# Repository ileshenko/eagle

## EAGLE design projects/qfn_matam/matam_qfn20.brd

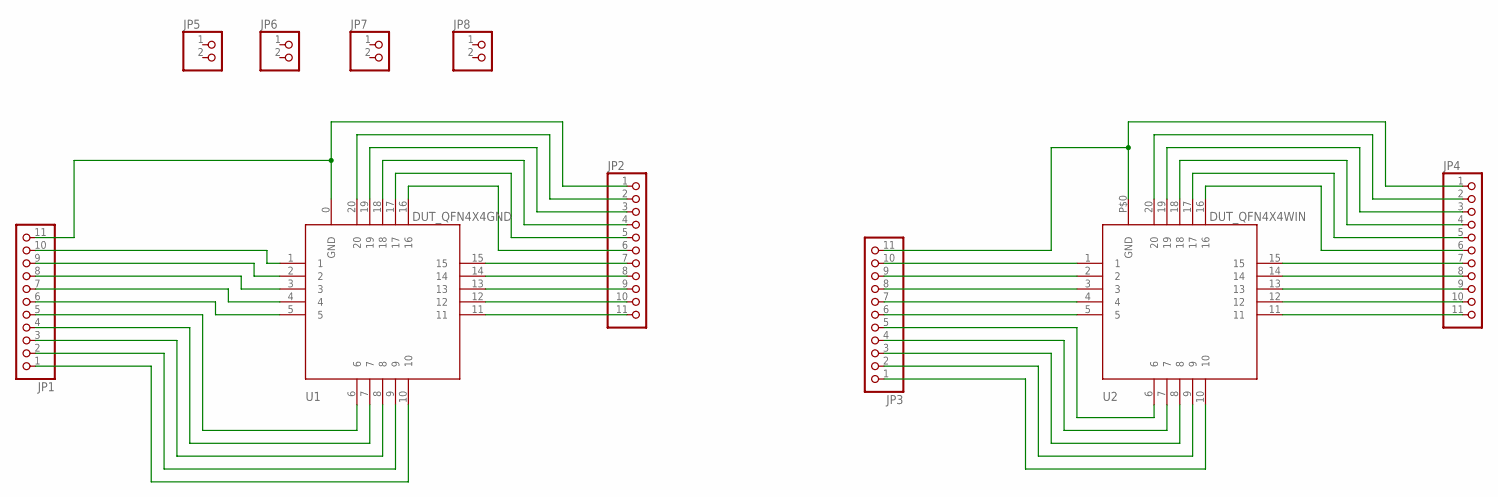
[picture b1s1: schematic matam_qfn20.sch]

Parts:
JP1, JP2, JP3, JP4: PINHD-1X11; 1X11
JP5, JP6, JP7, JP8: PINHD-1X2/90; 1X02/90
U1: DUT_QFN4X4GND; QFN20_4X4_GND
U2: DUT_QFN4X4WIN; QFN20_4X4_WINDOW

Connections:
unnamed: JP1.11, JP2.1, U1.0 (GND)
unnamed: JP1.10, U1.1
unnamed: JP1.9, U1.2
unnamed: JP1.8, U1.3
unnamed: JP1.7, U1.4
unnamed: JP1.6, U1.5
unnamed: JP1.5, U1.6
unnamed: JP1.4, U1.7
unnamed: JP1.3, U1.8
unnamed: JP1.2, U1.9
unnamed: JP1.1, U1.10
unnamed: JP2.11, U1.11
unnamed: JP2.10, U1.12
unnamed: JP2.9, U1.13
unnamed: JP2.8, U1.14
unnamed: JP2.7, U1.15
unnamed: JP2.6, U1.16
unnamed: JP2.5, U1.17
unnamed: JP2.4, U1.18
unnamed: JP2.3, U1.19
unnamed: JP2.2, U1.20
unnamed: JP3.10, U2.1
unnamed: JP3.9, U2.2
unnamed: JP3.8, U2.3
unnamed: JP3.7, U2.4
unnamed: JP3.6, U2.5
unnamed: JP3.5, U2.6
unnamed: JP3.4, U2.7
unnamed: JP3.3, U2.8
unnamed: JP3.2, U2.9
unnamed: JP3.1, U2.10
unnamed: JP3.11, JP4.1, U2.P$0 (GND)
unnamed: JP4.11, U2.11
unnamed: JP4.10, U2.12
unnamed: JP4.9, U2.13
unnamed: JP4.8, U2.14
unnamed: JP4.7, U2.15
unnamed: JP4.6, U2.16
unnamed: JP4.5, U2.17
unnamed: JP4.4, U2.18
unnamed: JP4.3, U2.19
unnamed: JP4.2, U2.20

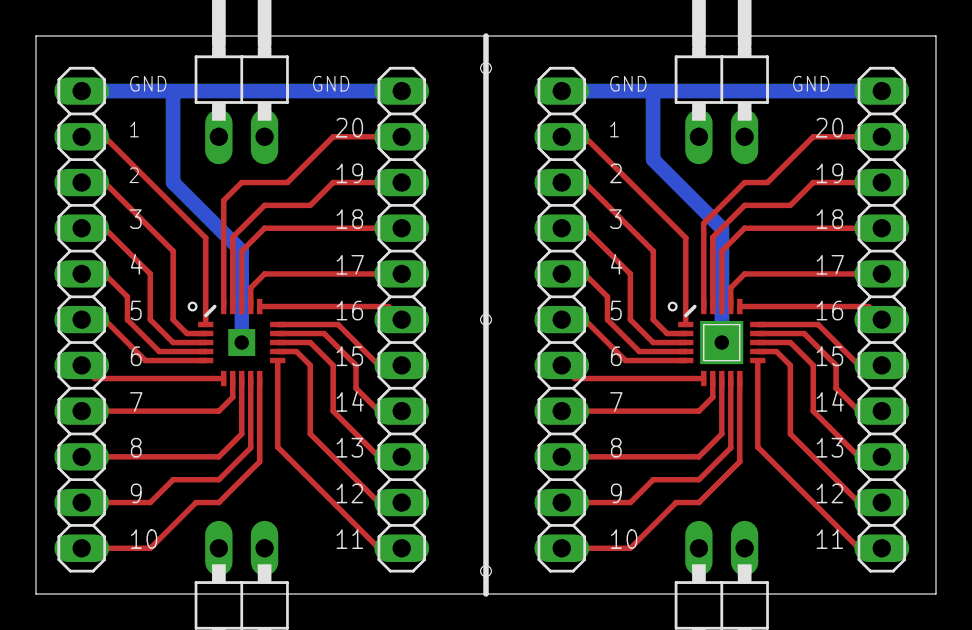
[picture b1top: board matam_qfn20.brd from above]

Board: 2 copper layers, 50.0 x 31.0 mm, 10 parts (0 on the bottom side), 42 nets.

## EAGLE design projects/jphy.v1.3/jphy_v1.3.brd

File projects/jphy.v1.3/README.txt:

Ver.1.3
Use IPC-73511 libraries for R and C

ver.1.2

Changes:
- Use 0805 devices instead of 1206;
- Use SMD LED and resistor;
- Change RJ45 drills from 2.54mm to 3mm.
- Change RJ45 ...

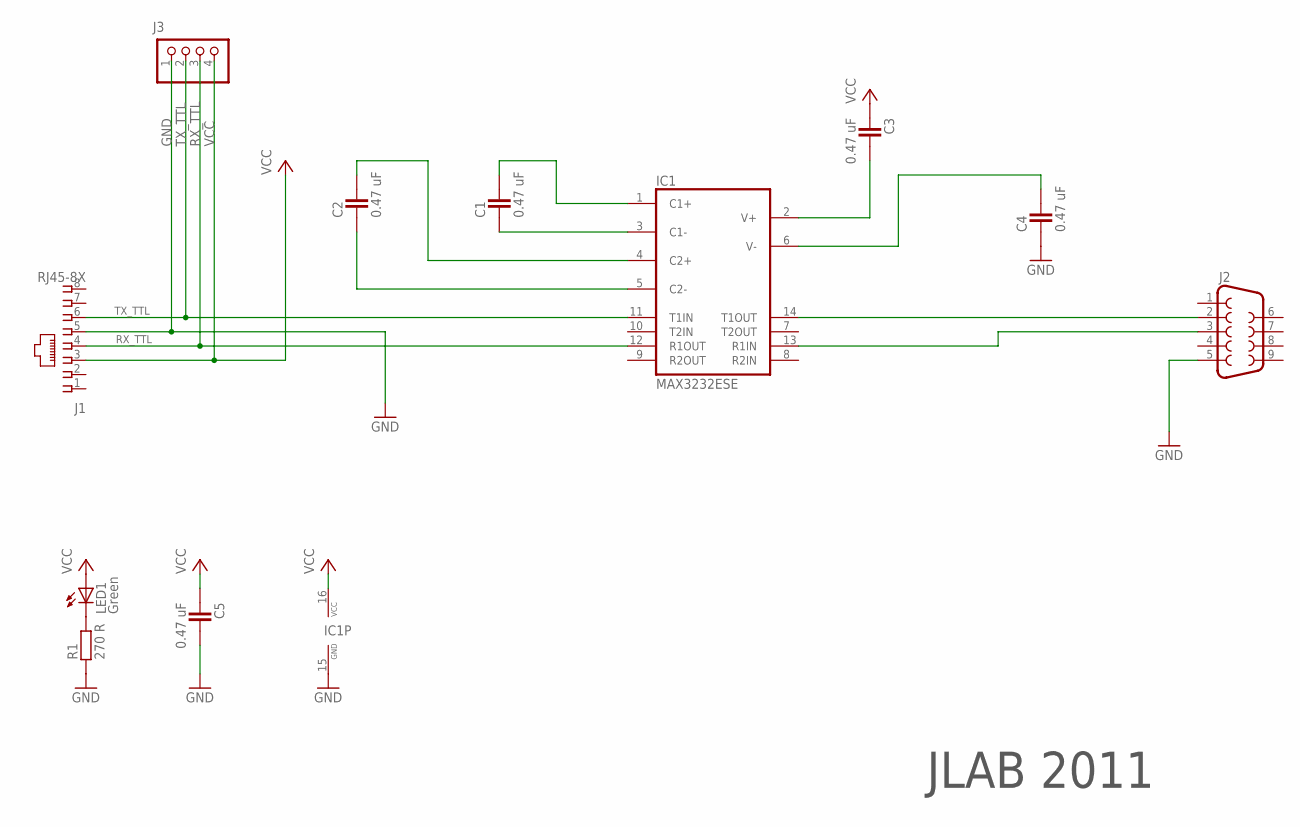
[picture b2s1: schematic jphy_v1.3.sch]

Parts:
C1, C2, C3, C4, C5: 0.47 uF; CAPC2012X145AN
IC1: MAX3232ESE; SO16
J1: RJ45-8X; RJ45-NO-SHIELD
J2: F09D
J3: PINHD-1X4; 1X04
LED1: Green; CHIP-LED0805
R1: 270 R; RESC2012X70N

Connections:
GND: C4.1, C5.2, IC1.15 (GND), J1.5, J2.5, J3.1, R1.1
unnamed: LED1.C, R1.2
unnamed: C3.2, IC1.2 (V+)
unnamed: C4.2, IC1.6 (V-)
unnamed: C1.1, IC1.3 (C1-)
unnamed: C1.2, IC1.1 (C1+)
unnamed: C2.1, IC1.5 (C2-)
unnamed: C2.2, IC1.4 (C2+)
unnamed: IC1.14 (T1OUT), J2.2
unnamed: IC1.13 (R1IN), J2.3
RX_TTL: IC1.12 (R1OUT), J1.4, J3.3
TX_TTL: IC1.11 (T1IN), J1.6, J3.2
VCC: C3.1, C5.1, IC1.16 (VCC), J1.3, J3.4, LED1.A

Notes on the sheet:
JLAB 2011

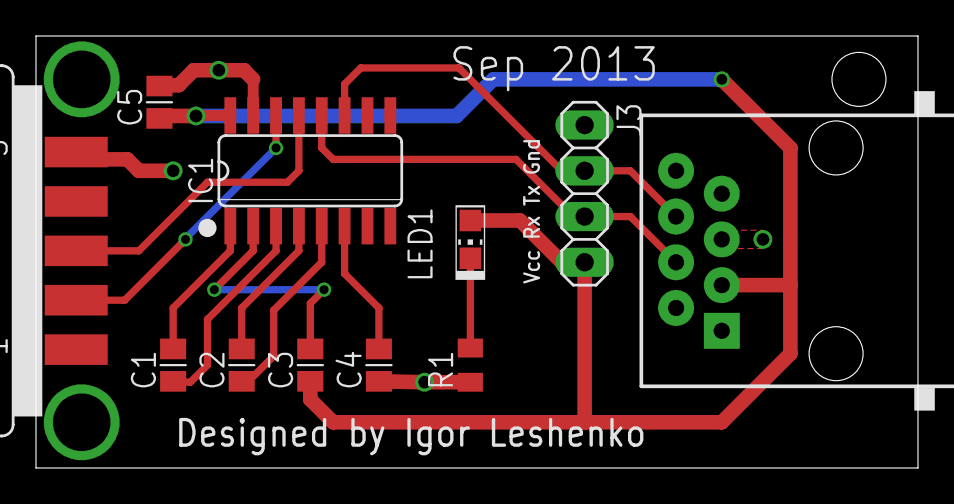
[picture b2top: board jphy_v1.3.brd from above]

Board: 2 copper layers, 49.0 x 24.0 mm, 11 parts (0 on the bottom side), 13 nets.

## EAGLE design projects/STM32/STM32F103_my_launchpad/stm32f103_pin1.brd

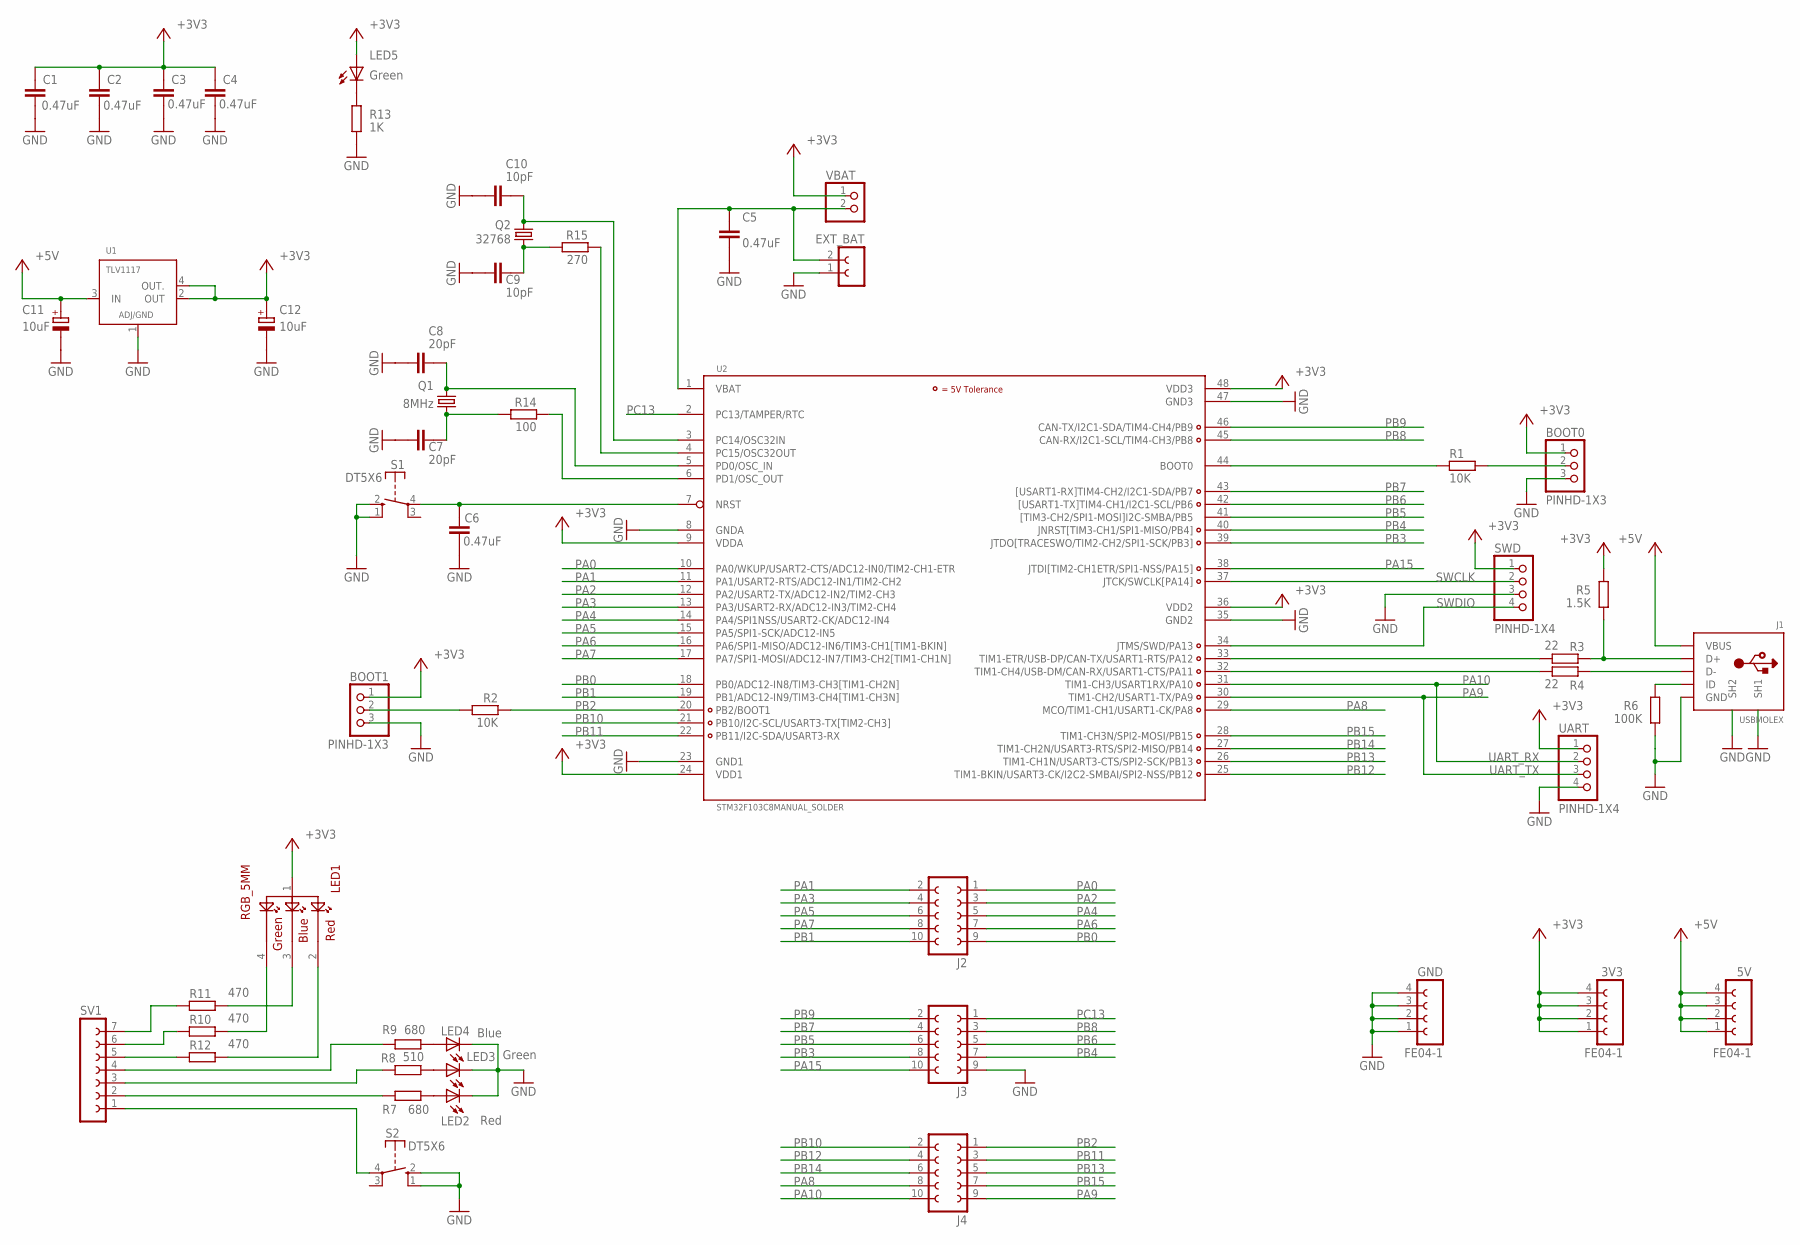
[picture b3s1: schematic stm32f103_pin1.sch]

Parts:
3V3, 5V: FE04-1
BOOT0, BOOT1: PINHD-1X3; 1X03
C1, C2, C3, C4, C5, C6: 0.47uF; CAPC2012X145AN
C7, C8: 20pF; CAPC2012X145AN
C9, C10: 10pF; CAPC2012X145AN
C11, C12: 10uF; CAPMP3216X180N
EXT_BAT: FE02-1
GND: FE04-1
J1: USBMOLEX; HW-MU-5F-20
J2, J3, J4: FE05-2
LED1: RGB_5MM
LED2: Red; CHIP-LED0805
LED3, LED5: Green; CHIP-LED0805
LED4: Blue; CHIP-LED0805
Q1: 8MHz; HC49/S
Q2: 32768; TC38H
R1, R2: 10K; RESC2012X70N
R3, R4: 22; RESC2012X70N
R5: 1.5K; RESC2012X70N
R6: 100K; RESC2012X70N
R7, R9: 680; RESC2012X70N
R8: 510; RESC2012X70N
R10, R11, R12: 470; RESC2012X70N
R13: 1K; RESC2012X70N
R14: 100; RESC2012X70N
R15: 270; RESC2012X70N
S1, S2: DT5X6; TACTILE-PTH
SV1: FE07-1; FE07
SWD: PINHD-1X4; 1X04
U1: TLV1117; SOT223-4
U2: STM32F103C8MANUAL_SOLDER; LQFP48_IGORL
UART: PINHD-1X4; 1X04
VBAT: PINHD-1X2; 1X02

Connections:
+3V3: 3V3.1, 3V3.2, 3V3.3, 3V3.4, BOOT0.1, BOOT1.1, C1.1, C2.1, C3.1, C4.1, C12.+, LED1.1, LED5.A, R5.2, SWD.1, U1.2 (OUT), U1.4 (OUT.), U2.9 (VDDA), U2.24 (VDD1), U2.36 (VDD2), U2.48 (VDD3), UART.1, VBAT.1
+5V: 5V.1, 5V.2, 5V.3, 5V.4, C11.+, J1.VBUS, U1.3 (IN)
BOOT0: R1.1, U2.44 (BOOT0)
BOOT1: BOOT1.2, R2.2
GND: BOOT0.3, BOOT1.3, C1.2, C2.2, C3.2, C4.2, C5.2, C6.2, C7.2, C8.2, C9.2, C10.2, C11.-, C12.-, EXT_BAT.1, GND.1, GND.2, GND.3, GND.4, J1.GND, J1.SH1, J1.SH2, J3.9, LED2.C, LED3.C, LED4.C, R6.2, R13.1, S1.1 (S), S1.2 (S), S2.1 (S), S2.2 (S), SWD.3, U1.1 (ADJ/GND), U2.8 (GNDA), U2.23 (GND1), U2.35 (GND2), U2.47 (GND3), UART.4
unnamed: R12.1, SV1.5
unnamed: R15.1, U2.4 (PC15/OSC32OUT)
unnamed: C7.1, Q1.1, R14.2
unnamed: C10.1, Q2.2, U2.3 (PC14/OSC32IN)
unnamed: C6.1, S1.4, U2.7 (NRST)
unnamed: C9.1, Q2.1, R15.2
unnamed: BOOT0.2, R1.2
unnamed: C8.1, Q1.2, U2.5 (PD0/OSC_IN)
unnamed: R14.1, U2.6 (PD1/OSC_OUT)
unnamed: LED5.C, R13.2
unnamed: J1.D+, R3.1, R5.1
unnamed: J1.D-, R4.1
unnamed: J1.ID, R6.1
unnamed: S2.4, SV1.1
unnamed: LED2.A, R7.2
unnamed: LED3.A, R8.2
unnamed: LED4.A, R9.2
unnamed: R7.1, SV1.2
unnamed: R8.1, SV1.3
unnamed: R9.1, SV1.4
unnamed: LED1.2, R12.2
unnamed: LED1.3, R11.2
unnamed: LED1.4, R10.2
unnamed: R10.1, SV1.6
unnamed: R11.1, SV1.7
PA0: J2.1, U2.10 (PA0/WKUP/USART2-CTS/ADC12-IN0/TIM2-CH1-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)
PA1: J2.2, U2.11 (PA1/USART2-RTS/ADC12-IN1/TIM2-CH2)
PA2: J2.3, U2.12 (PA2/USART2-TX/ADC12-IN2/TIM2-CH3)
PA3: J2.4, U2.13 (PA3/USART2-RX/ADC12-IN3/TIM2-CH4)
PA4: J2.5, U2.14 (PA4/SPI1NSS/USART2-CK/ADC12-IN4)
PA5: J2.6, U2.15 (PA5/SPI1-SCK/ADC12-IN5)
PA6: J2.7, U2.16 (PA6/SPI1-MISO/ADC12-IN6/TIM3-CH1[TIM1-B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)
PA7: J2.8, U2.17 (PA7/SPI1-MOSI/ADC12-IN7/TIM3-CH2[TIM1-C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)
PA8: J4.8, U2.29 (MCO/TIM1-CH1/USART1-CK/PA8)
PA9: J4.9, U2.30 (TIM1-CH2/USART1-TX/PA9), UART.3
PA10: J4.10, U2.31 (TIM1-CH3/USART1RX/PA10), UART.2
PA11: R4.2, U2.32 (TIM1-CH4/USB-DM/CAN-RX/USART1-CTS/PA11)
PA12: R3.2, U2.33 (TIM1-ETR/USB-DP/CAN-TX/USART1-RTS/PA12)
PA13: SWD.4, U2.34 (JTMS/SWD/PA13)
PA14: SWD.2, U2.37 (JTCK/SWCLK[PA14])
PA15: J3.10, U2.38 (JTDI[TIM2-CH1ETR/SPI1-NSS/PA15])
PB0: J2.9, U2.18 (PB0/ADC12-IN8/TIM3-CH3[TIM1-CH2N])
PB1: J2.10, U2.19 (PB1/ADC12-IN9/TIM3-CH4[TIM1-CH3N])
PB2: J4.1, R2.1, U2.20 (PB2/BOOT1)
PB3: J3.8, U2.39 (JTDO[TRACESWO/TIM2-CH2/SPI1-SCK/PB3])
PB4: J3.7, U2.40 (JNRST[TIM3-CH1/SPI1-MISO/PB4])
PB5: J3.6, U2.41 ([TIM3-CH2/SPI1-MOSI]I2C-SMBA/PB5)
PB6: J3.5, U2.42 ([USART1-TX]TIM4-CH1/I2C1-SCL/PB6)
PB7: J3.4, U2.43 ([USART1-RX]TIM4-CH2/I2C1-SDA/PB7)
PB8: J3.3, U2.45 (CAN-RX/I2C1-SCL/TIM4-CH3/PB8)
PB9: J3.2, U2.46 (CAN-TX/I2C1-SDA/TIM4-CH4/PB9)
PB10: J4.2, U2.21 (PB10/I2C-SCL/USART3-TX[TIM2-CH3])
PB11: J4.3, U2.22 (PB11/I2C-SDA/USART3-RX)
PB12: J4.4, U2.25 (TIM1-BKIN/USART3-CK/I2C2-SMBAI/SPI2-NSS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)
PB13: J4.5, U2.26 (TIM1-CH1N/USART3-CTS/SPI2-SCK/PB13)
PB14: J4.6, U2.27 (TIM1-CH2N/USART3-RTS/SPI2-MISO/PB14)
PB15: J4.7, U2.28 (TIM1-CH3N/SPI2-MOSI/PB15)
PC13: J3.1, U2.2 (PC13/TAMPER/RTC)
VBAT: C5.1, EXT_BAT.2, U2.1 (VBAT), VBAT.2

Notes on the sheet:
UART_TX
UART_RX
SWDIO
SWCLK

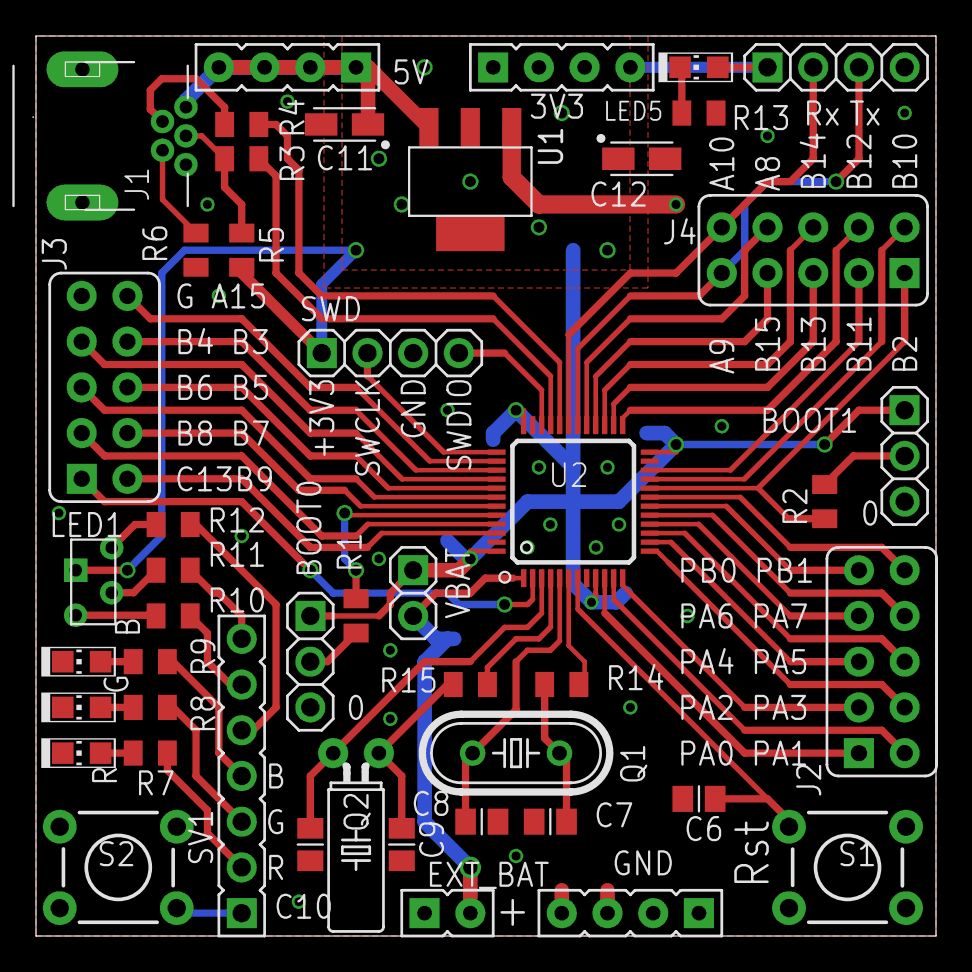
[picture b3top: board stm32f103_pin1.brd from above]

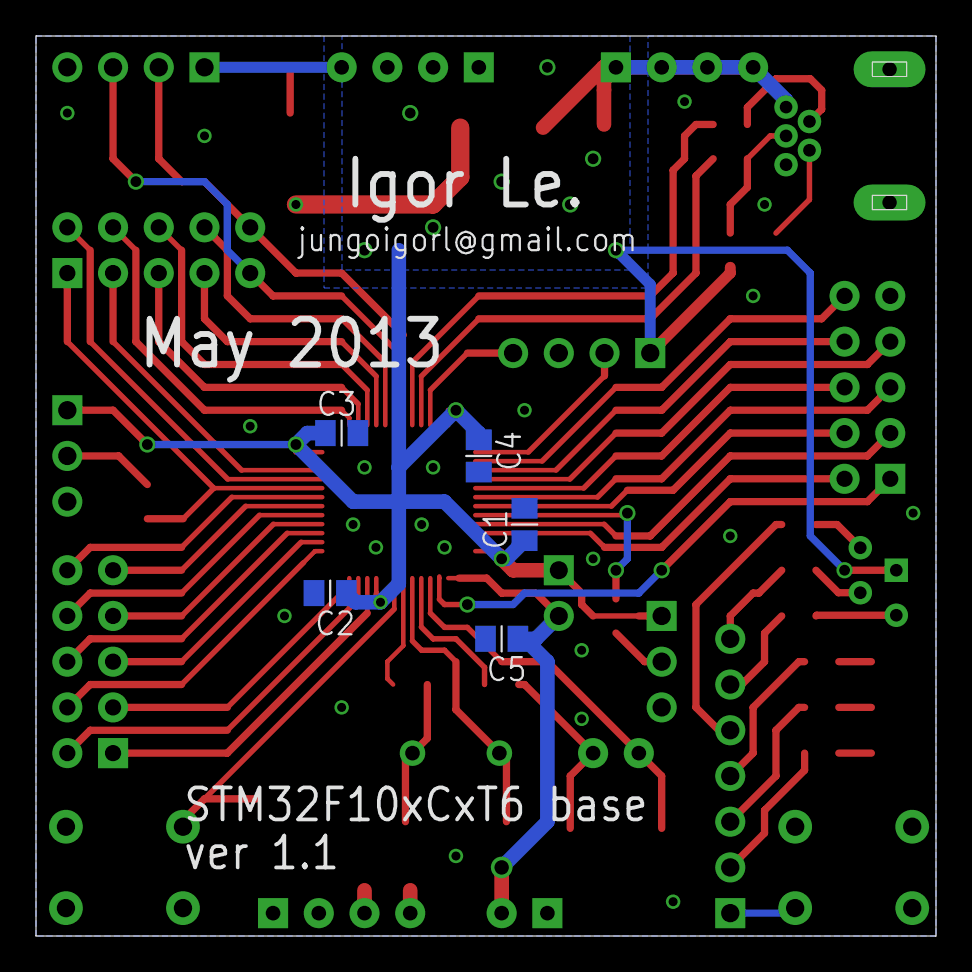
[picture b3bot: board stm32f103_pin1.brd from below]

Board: 2 copper layers, 50.0 x 50.0 mm, 52 parts (5 on the bottom side), 64 nets.

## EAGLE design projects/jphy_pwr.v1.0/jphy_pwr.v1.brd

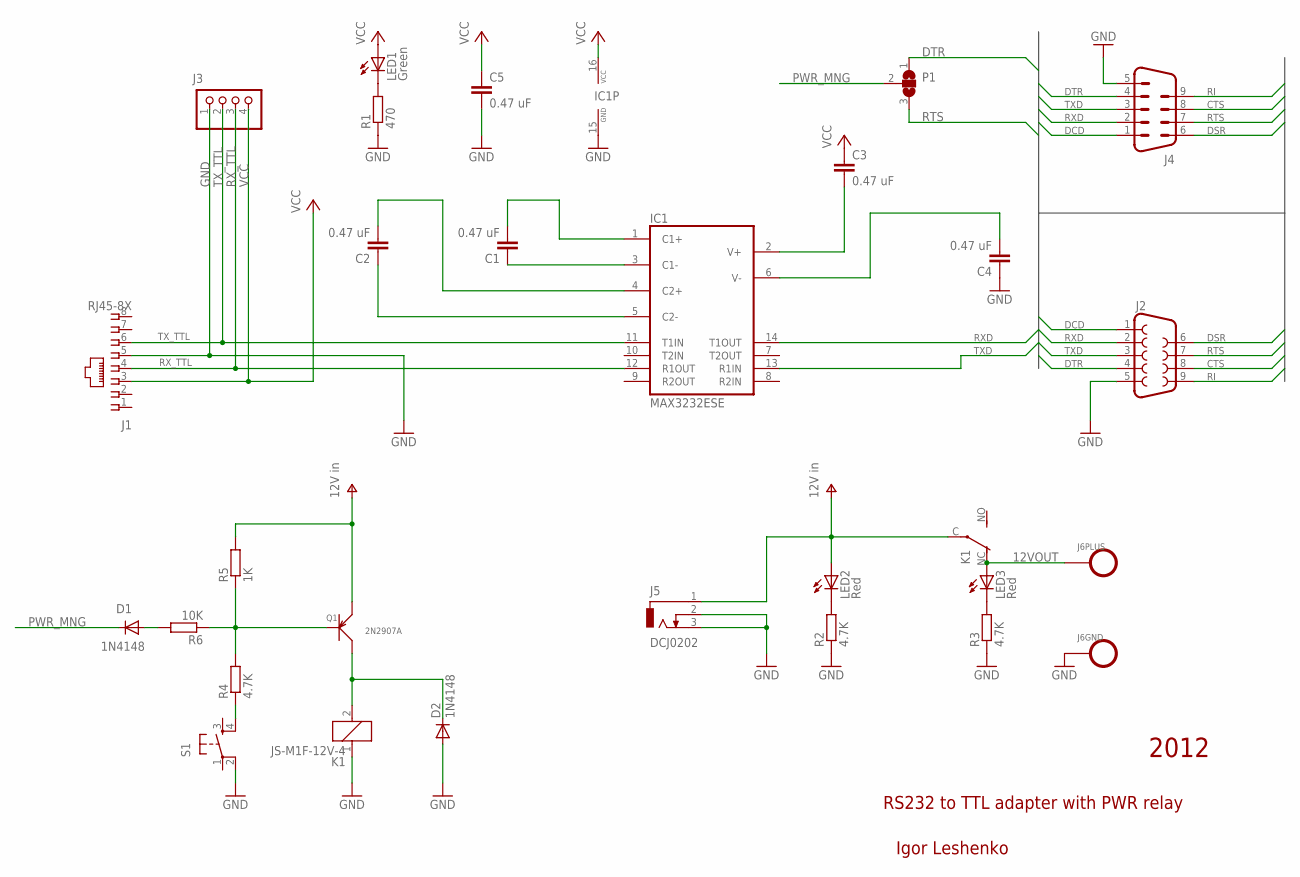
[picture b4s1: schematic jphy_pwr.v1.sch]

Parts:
C1, C2, C3, C4: 0.47 uF; C0805
C5: 0.47 uF; C1206
D1, D2: 1N4148; D-5
IC1: MAX3232ESE; SO16
J1: RJ45-8X; RJ45-NO-SHIELD
J2: F09D
J3: PINHD-1X4; 1X04
J4: M09D
J5: DCJ0202
J6: POWER-OUT; FLEX-POWER
K1: JS-M1F-12V-4; JS-M
LED1: Green; LED3MM
LED2, LED3: Red; LED3MM
P1: PAD-SOLDERJUMPER-2WAYT; 3P-SMD-4.8X2
Q1: 2N2907A; TO-92-TRIANGLE
R1: 470; 0207/2V
R2, R3, R4: 4.7K; 0207/2V
R5: 1K; 0207/2V
R6: 10K; 0207/2V
S1: TAC_SWITCHPTH; TACTILE-PTH

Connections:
12VOUT: J6.1, K1.NC (O), LED3.A
+12V: J5.1, K1.C, LED2.A, Q1.1 (E), R5.2
CTS: J2.8, J4.8
DCD: J2.1, J4.1
DSR: J2.6, J4.6
DTR: J2.4, J4.4, P1.1
GND: C4.1, C5.2, D2.A, IC1.15 (GND), J1.5, J2.5, J3.1, J4.5, J5.2, J5.3, J6.2, K1.1, R1.1, R2.1, R3.1, S1.2
unnamed: LED1.K (C), R1.2
unnamed: C3.2, IC1.2 (V+)
unnamed: C4.2, IC1.6 (V-)
unnamed: C1.1, IC1.3 (C1-)
unnamed: C1.2, IC1.1 (C1+)
unnamed: C2.1, IC1.5 (C2-)
unnamed: C2.2, IC1.4 (C2+)
unnamed: LED2.K (C), R2.2
unnamed: LED3.K (C), R3.2
unnamed: D2.C, K1.2, Q1.3 (C)
unnamed: R4.1, S1.4
unnamed: D1.A, R6.2
unnamed: Q1.2 (B), R4.2, R5.1, R6.1
PWR_MNG: D1.C, P1.2
RI: J2.9, J4.9
RTS: J2.7, J4.7, P1.3
RXD: IC1.14 (T1OUT), J2.2, J4.2
RX_TTL: IC1.12 (R1OUT), J1.4, J3.3
TXD: IC1.13 (R1IN), J2.3, J4.3
TX_TTL: IC1.11 (T1IN), J1.6, J3.2
VCC: C3.1, C5.1, IC1.16 (VCC), J1.3, J3.4, LED1.A

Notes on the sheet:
RS232 to TTL adapter with PWR relay
Igor Leshenko
2012

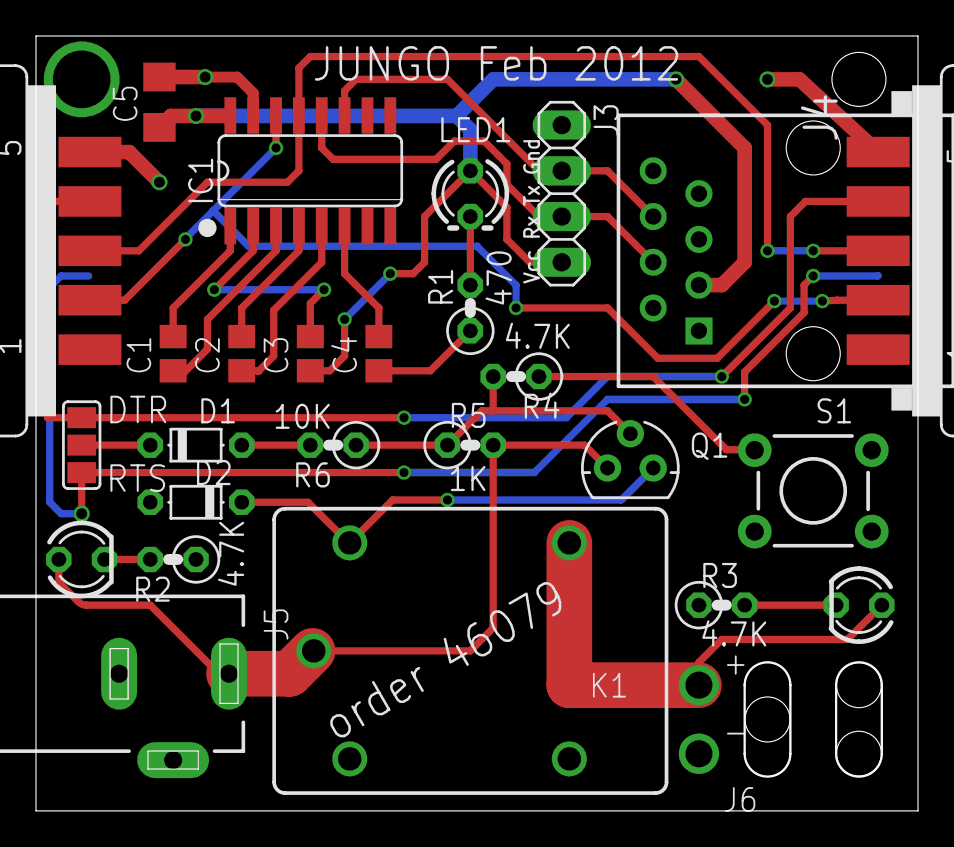
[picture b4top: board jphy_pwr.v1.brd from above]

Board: 2 copper layers, 48.9 x 42.9 mm, 27 parts (0 on the bottom side), 28 nets.

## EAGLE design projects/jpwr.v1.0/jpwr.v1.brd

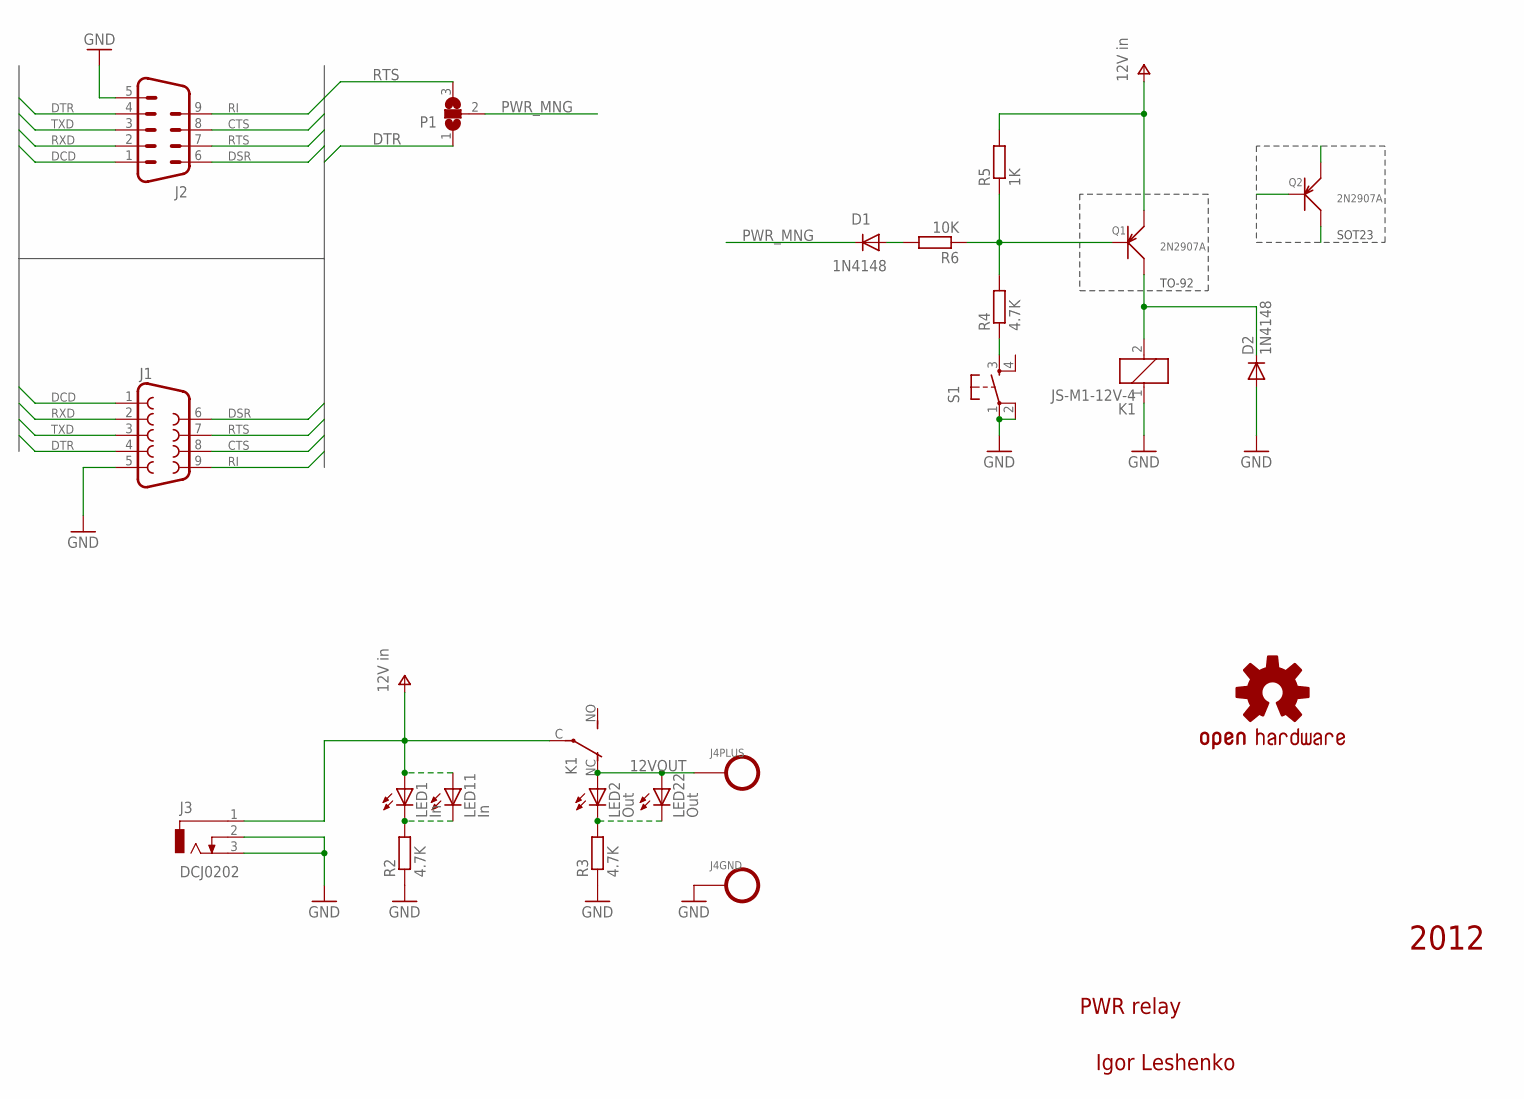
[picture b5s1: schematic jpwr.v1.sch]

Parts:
D1, D2: 1N4148; SOD123
J1: F09D
J2: M09D
J3: DCJ0202
J4: POWER-OUT; FLEX-POWER
K1: JS-M1-12V-4; SRD; MPN JSM1-12V-4
LED1, LED11: In; CHIPLED_0805
LED2, LED22: Out; CHIPLED_0805
P1: PAD-SOLDERJUMPER-2WAYT; 3P-SMD-4.8X2
Q1: 2N2907A; TO-92-TRIANGLE
Q2: 2N2907A; SOT23
R2, R3, R4: 4.7K; M0805
R5: 1K; M0805
R6: 10K; M0805
S1: TAC_SWITCHPTH; TACTILE-PTH
U$1: OSHW-LOGOL; OSHW-LOGO-L

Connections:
12VOUT: J4.1, K1.NC (O), LED2.A, LED22.A
+12V: J3.1, K1.C, LED1.A, LED11.A, Q1.1 (E), Q2.2 (E), R5.2
CTS: J1.8, J2.8
DCD: J1.1, J2.1
DSR: J1.6, J2.6
DTR: J1.4, J2.4, P1.1
GND: D2.A, J1.5, J2.5, J3.2, J3.3, J4.2, K1.1, R2.1, R3.1, S1.1, S1.2
unnamed: R4.1, S1.3
unnamed: LED1.C, LED11.C, R2.2
unnamed: LED2.C, LED22.C, R3.2
unnamed: D1.A, R6.2
PWR_MNG: D1.C, P1.2
Q1_B: Q1.2 (B), Q2.1 (B), R4.2, R5.1, R6.1
Q1_C: D2.C, K1.2, Q1.3 (C), Q2.3 (C)
RI: J1.9, J2.9
RTS: J1.7, J2.7, P1.3
RXD: J1.2, J2.2
TXD: J1.3, J2.3

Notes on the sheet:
PWR relay
Igor Leshenko
2012
TO-92
SOT23

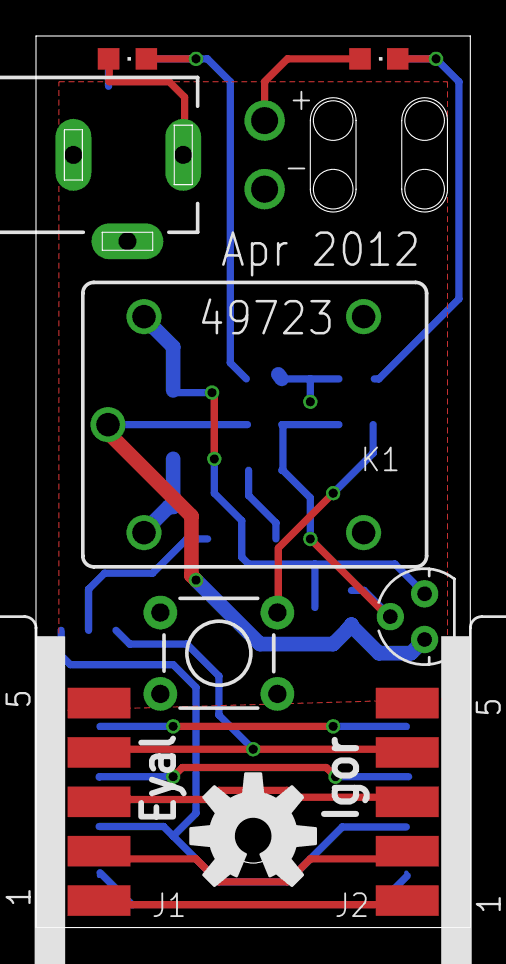
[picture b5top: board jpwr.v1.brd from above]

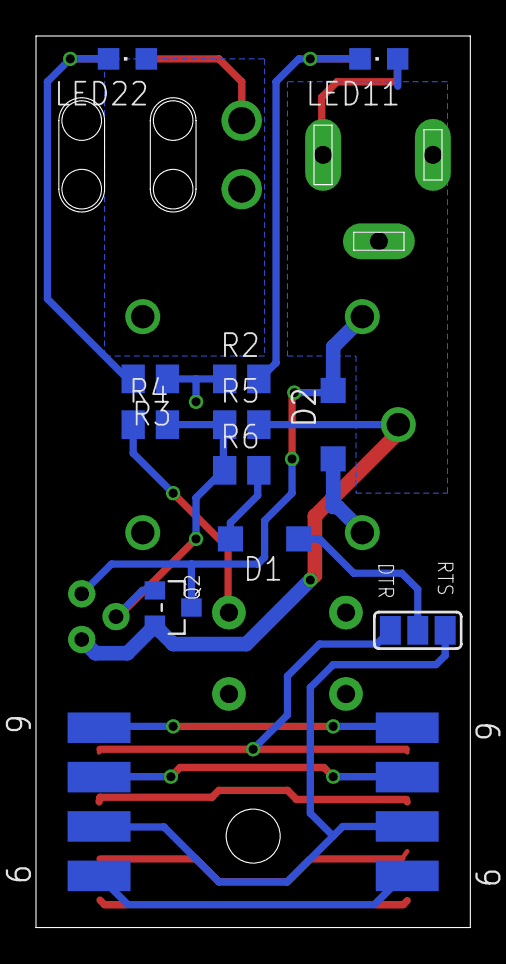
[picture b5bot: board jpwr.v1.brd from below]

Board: 2 copper layers, 24.1 x 49.5 mm, 21 parts (11 on the bottom side), 18 nets.

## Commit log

2013-03-17 LEt's try to organize all my Eagle stuff in single repository
2013-03-19 PLM Version 1.0 Finished and sent to PCB house
2013-03-21 return back Dimach directory, moved by mistake
2013-05-27 Fix button layout
2013-05-27 Fix LQFP48 footprint
2013-05-27 stm32 launchpad ver 1.1
2013-09-23 fix typo on STM32 launchpad
2013-09-23 begin jphy.v1.3 directory from v1.2
2013-09-23 JPHY ver 1.3 (300 pcs)
2014-01-27 Save all stuff in single repository. Before separation
2014-03-05 update used libraries list. FTDI - change 3V3 from OUT to POWER type
2014-05-31 ignore eagle project
2014-05-31 QFN20 adapter for matam
2014-07-02 update lib_used according to old projects
2014-07-03 update used libraries
2014-07-05 update user libraryes list
2014-07-05 remove eagle project files from repository
2014-07-05 boiler room indicator - allign leds brightness
2014-07-05 save unfinished changes in boiler schematics
2014-07-21 minimize freezed boiler_temp directory

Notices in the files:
parts and their libraries:
SparkFun-FreqCtrl: Licensing: CC v3.0 Share-Alike You are welcome to use this library for commercial purposes.
